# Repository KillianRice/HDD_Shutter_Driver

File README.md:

# HDD_Shutter_Driver #

HDD shutter driver circuit based on Rob Scholten's 2007 RSI paper (see below). Modifications include the option of using an IXYS IXDF604PI (about $2/IC) instead of the TI LMD18200 (about $17/IC) to drive the shutter. 

## Notes ##
- Outputs are to standard BNC connectors so care should be taken to avoid shorting to ground. 
- H3 (PWR_SEL) allows using a single voltage supply to power the IC and provide current for the shutter. 
- H1 and H2 allow the selection of the output polarity (OUT_1x when using the IXDF604PI, OUT_2x when using LMD18200). 

## Ordering ##
### Shutter Driver ###
The main circuit for driving HDD shutters. 

- v1.1: <a href="https://oshpark.com/shared_projects/gJmzOIRQ">Shutter Driver Rev. 1.1 (OSH Park)</a>

- v1.0: <a href="https://oshpark.com/shared_projects/CgeGIYMU">Shutter Driver Rev. 1.0 (OSH Park)</a>

### Power Distribution ###
Circuit used to breakout a power supply for multiple shutter driver boards. 
- v1.1: **Add notes**
- v1.0: <a href="https://oshpark.com/shared_projects/fE8gVI9B">Positive Power Distribution Rev. 1.0 (OSH Park)</a>

## Original paper ## 
Enhanced laser shutter using a hard disk drive rotary voice-coil actuator

R. E. Scholten

Review of Scientific Instruments <b>78</b>, 026101 (2007)

https://doi.org/10.1063/1.2437199

## Also see ##
- <a href="https://github.com/JQIamo/hard-drive-shutter">JQI's hard-drive-shutter</a>

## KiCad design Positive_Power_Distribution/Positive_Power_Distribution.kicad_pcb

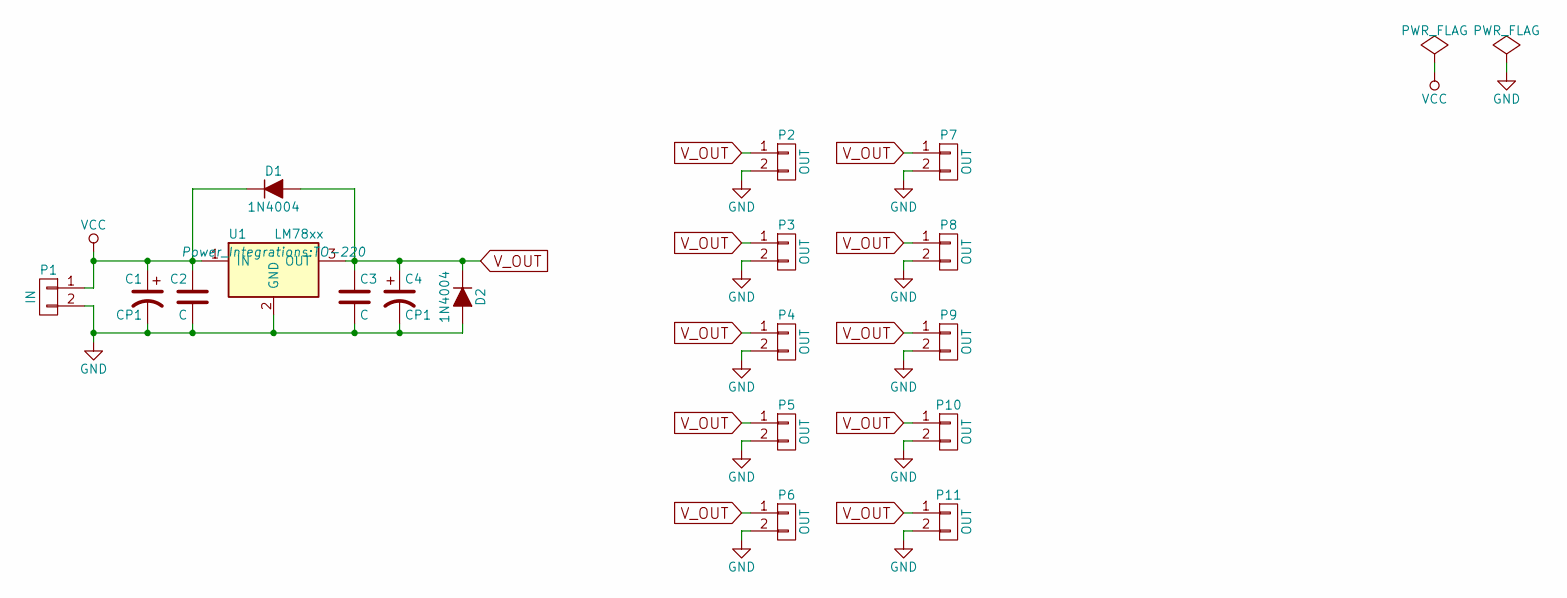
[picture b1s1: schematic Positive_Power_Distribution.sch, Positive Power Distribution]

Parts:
C1: CP1; CP_Radial_D10.0mm_P5.00mm
C2, C3: C; C_Disc_D5.0mm_W2.5mm_P5.00mm
C4: CP1; CP_Radial_D5.0mm_P2.00mm
D1, D2: 1N4004; D_DO-41_SOD81_P10.16mm_Horizontal
P1: IN; Socket_MOLEX-KK-RM2-54mm_Lock_2pin_straight
P2, P3, P4, P5, P6, P7, P8, P9, P10, P11: OUT; Socket_MOLEX-KK-RM2-54mm_Lock_2pin_straight
U1: LM78xx; TO-220

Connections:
GND: C1.2, C2.2, C3.2, C4.2, D2.2 (A), P1.2, P2.2, P3.2, P4.2, P5.2, P6.2, P7.2, P8.2, P9.2, P10.2, P11.2, U1.2 (GND)
VCC: C1.1, C2.1, D1.1 (K), P1.1, U1.1 (IN)
V_OUT: C3.1, C4.1, D1.2 (A), D2.1 (K), P2.1, P3.1, P4.1, P5.1, P6.1, P7.1, P8.1, P9.1, P10.1, P11.1, U1.3 (OUT)

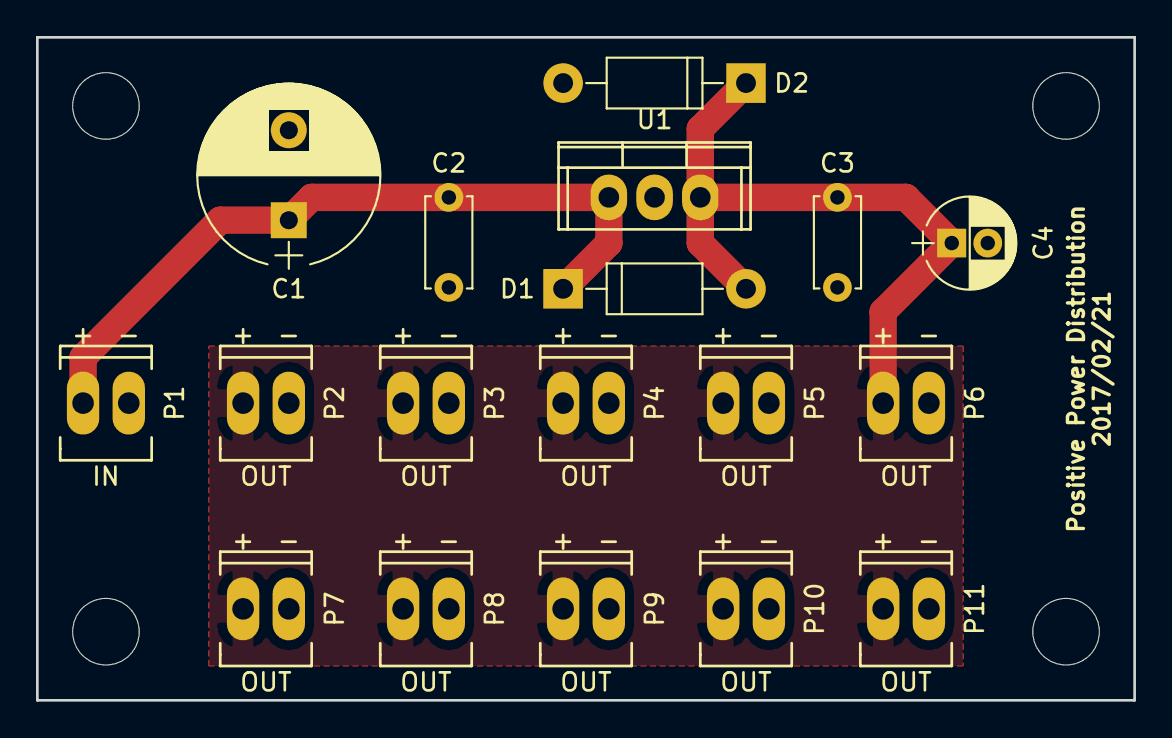
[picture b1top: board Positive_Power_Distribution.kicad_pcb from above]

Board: 2 copper layers, 61.0 x 36.8 mm, 18 parts (0 on the bottom side), 3 nets.

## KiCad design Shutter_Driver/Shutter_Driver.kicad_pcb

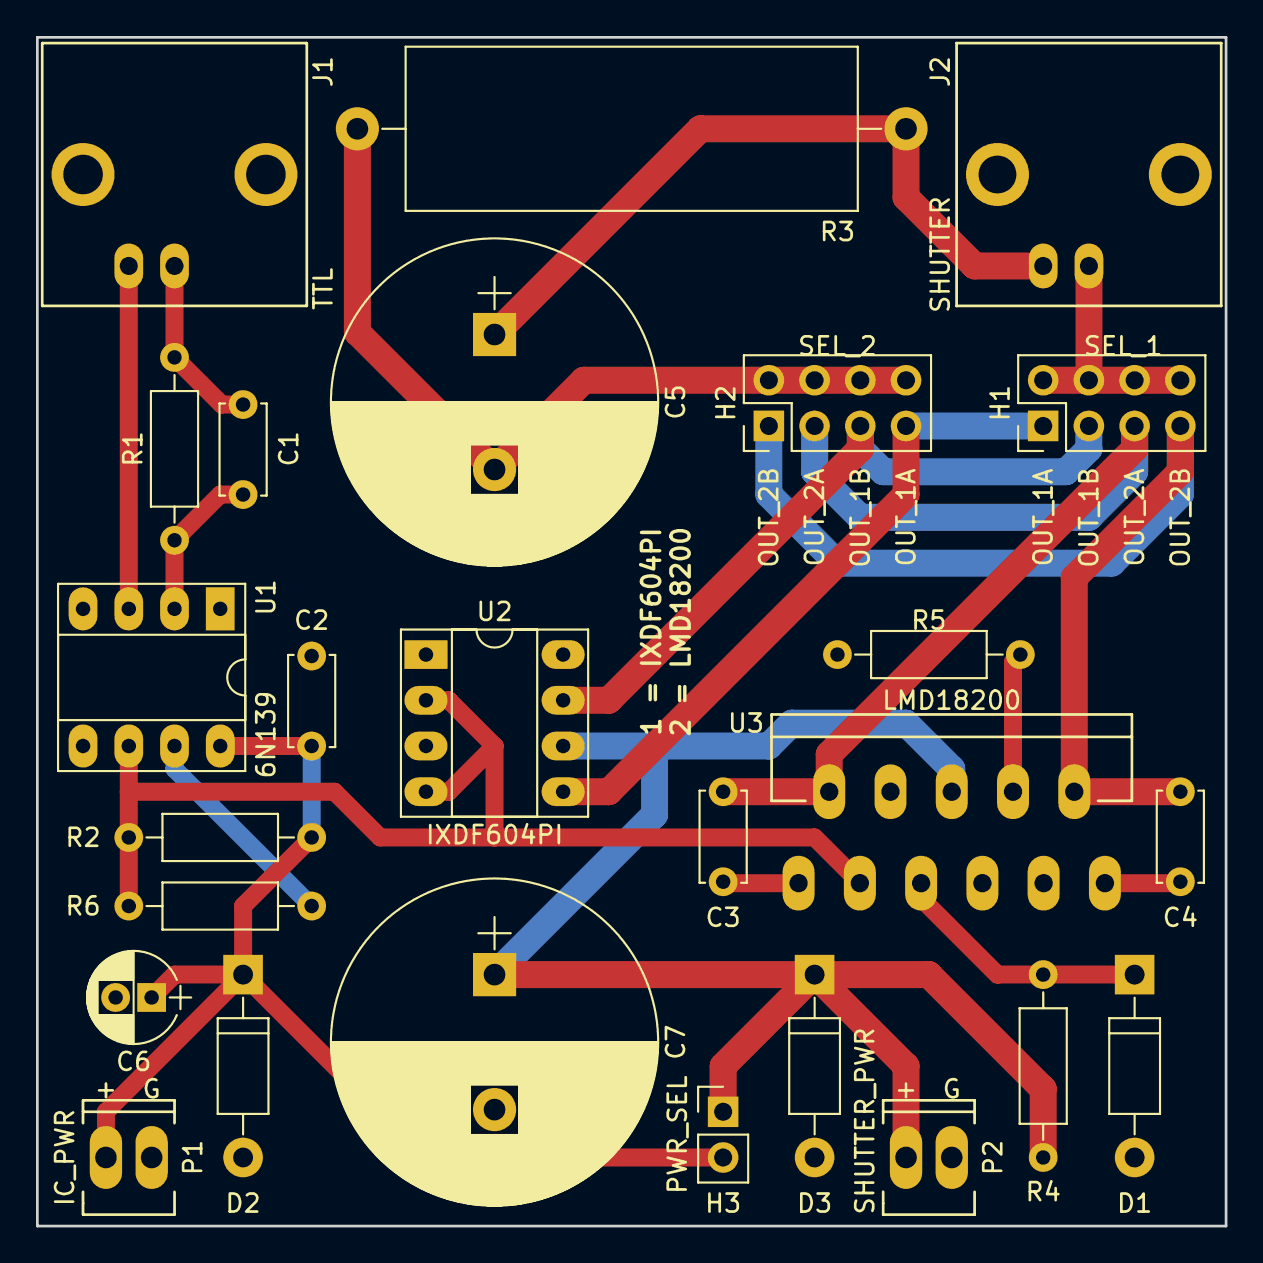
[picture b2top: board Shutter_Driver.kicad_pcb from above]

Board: 2 copper layers, 66.0 x 66.0 mm, 26 parts (0 on the bottom side), 19 nets.

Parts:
C1: CP; C_Disc_D5.0mm_W2.5mm_P5.00mm
C2: 0.1uF; C_Disc_D5.0mm_W2.5mm_P5.00mm
C3, C4: 10nF; C_Disc_D5.0mm_W2.5mm_P5.00mm
C5: C; CP_Radial_D18.0mm_P7.50mm
C6: 10uF; CP_Radial_D5.0mm_P2.00mm
C7: 2500uF; CP_Radial_D18.0mm_P7.50mm
D1: 5.6V; D_DO-41_SOD81_P10.16mm_Horizontal
D2, D3: D; D_DO-41_SOD81_P10.16mm_Horizontal
H1: SEL_1; Pin_Header_Straight_2x04_Pitch2.54mm
H2: SEL_2; Pin_Header_Straight_2x04_Pitch2.54mm
H3: PWR_SEL; Pin_Header_Straight_1x02_Pitch2.54mm
J1: TTL; BNC_Socket_TYCO-AMP_LargePads
J2: SHUTTER; BNC_Socket_TYCO-AMP_LargePads
P1: IC_PWR; Socket_MOLEX-KK-RM2-54mm_Lock_2pin_straight
P2: SHUTTER_PWR; Socket_MOLEX-KK-RM2-54mm_Lock_2pin_straight
R1: RI; R_Axial_DIN0207_L6.3mm_D2.5mm_P10.16mm_Horizontal
R2: RL; R_Axial_DIN0207_L6.3mm_D2.5mm_P10.16mm_Horizontal
R3: R; R_Axial_Power_L25.0mm_W9.0mm_P30.48mm
R4: 10k; R_Axial_DIN0207_L6.3mm_D2.5mm_P10.16mm_Horizontal
R5: 2.7k; R_Axial_DIN0207_L6.3mm_D2.5mm_P10.16mm_Horizontal
R6: R; R_Axial_DIN0207_L6.3mm_D2.5mm_P10.16mm_Horizontal
U1: 6N139; DIP-8_W7.62mm_Socket_LongPads
U2: IXDF604PI; DIP-8_W7.62mm_Socket_LongPads
U3: LMD18200; Multiwatt_15_Vertical

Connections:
+5V: C2.1, C6.1, D2.1, H3.2, P1.1, R2.2, U1.8
GND: C2.2, C6.2, C7.2, D1.2, D2.2, D3.2, P1.2, P2.2, R5.2, U1.5, U2.3, U3.4, U3.7
LOGIC: R2.1, R6.2, U1.6, U2.2, U2.4, U3.3
unnamed: C1.1, R1.1, U1.2
unnamed: C1.2, J1.1, R1.2
unnamed: C3.2, U3.1
unnamed: C4.2, U3.11
unnamed: C5.1, J2.2, R3.2
unnamed: C5.2, H2.2, H2.4, H2.6, H2.8, R3.1
unnamed: D1.1, R4.1, U3.5
unnamed: H1.2, H1.4, H1.6, H1.8, J2.1
unnamed: J1.2, U1.3
unnamed: R5.1, U3.8
unnamed: R6.1, U1.7
OUT_1A: H1.1, H2.7, U2.5
OUT_1B: H1.3, H2.5, U2.7
OUT_2A: C3.1, H1.5, H2.3, U3.2
OUT_2B: C4.1, H1.7, H2.1, U3.10
VCC: C7.1, D3.1, H3.1, P2.1, R4.2, U2.6, U3.6

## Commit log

2017-12-01 Updated .gitignore for KiCad files
2017-12-01 Added KiCad files
2017-12-02 Rename Shutter_Driver.kicad_pcb to Shutter_Driver/Shutter_Driver.kicad_pcb
2017-12-02 Rename Shutter_Driver.net to Shutter_Driver/Shutter_Driver.net
2017-12-02 Rename Shutter_Driver.pro to Shutter_Driver/Shutter_Driver.pro
2017-12-02 Rename Shutter_Driver.sch to Shutter_Driver/Shutter_Driver.sch
2017-12-02 Added Shutter_Driver schematic PDF
2017-12-02 Added Positive_Power_Distribution circuit
    This circuit is used to breakout the power connections for multiple shutter drivers.
2017-12-02 Rename Library/6N139.lib to Shuter_Driver/6N139.lib
2017-12-02 Rename Shuter_Driver/6N139.lib to Shutter_Driver/Library/6N139.lib
2017-12-02 Rename Library/IXDF604.lib to Shutter_Driver/Library/IXDF604.lib
2017-12-02 Rename Library/LMD18200.lib to Shutter_Driver/Library/LMD18200.lib
2017-12-02 Rename Library/optocoupler-2.lib to Shutter_Driver/Library/optocoupler-2.lib
2017-12-05 Create LICENSE
2017-12-05 Added Shutter_Driver-cache.lib
2017-12-05 Added Positive_Power_Distribution-cache.lib
2017-12-06 Rename Shutter_Driver/Library/6N139.lib to Shutter_Driver/library/6N139.lib
2017-12-06 Rename Shutter_Driver/Library/IXDF604.lib to Shutter_Driver/library/IXDF604.lib
2017-12-06 Rename Shutter_Driver/Library/optocoupler-2.lib to Shutter_Driver/library/optocoupler-2.lib
2017-12-06 Rename Shutter_Driver/Library/LMD18200.lib to Shutter_Driver/library/LMD18200.lib
2017-12-06 Updated files.
2018-02-11 Add files via upload
    Uploaded Gerber files.
2018-02-11 Add files via upload
    Separated PTH (plated through holes) and NPTH (non-plated through holes) in .drl file.
2018-02-11 Added Gerber and drill files.
    Drill file has PTH and NPTH separated into two .drl files.
